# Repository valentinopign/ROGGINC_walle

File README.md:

# ROGGINC_walle
Proyecto final que encabezamos durante nuestra estadia en 7mo año para la materia de "Proyecto y diseño electronico"

Inspirados por la icónica película de Disney, tomamos la decisión
de modelar nuestro proyecto tomando la forma del entrañable
personaje principal, Wall-E. Este robot carismático se ha
convertido en un ícono, y decidimos emular su diseño distintivo
para crear un dispositivo interactivo y encantador.
Para lograr este objetivo, optamos por utilizar la tecnología de
impresión 3D para recrear no solo la forma general de Wall-E,
sino también sus característicos engranajes, añadiendo
autenticidad y detalle a nuestro proyecto. La impresión 3D nos
proporcionó la flexibilidad necesaria para capturar la esencia del
personaje de manera precisa y personalizada.
El enfoque principal de nuestro proyecto fue desarrollar un robot
capaz de moverse e interactuar de manera amigable con las
personas, y la elección de Wall-E como inspiración nos
proporcionó una base sólida para lograr este objetivo. Su diseño
único y su personalidad afectuosa sirvieron como punto de
partida para crear un dispositivo que no solo fuera funcional, sino
también emocionalmente atractivo.

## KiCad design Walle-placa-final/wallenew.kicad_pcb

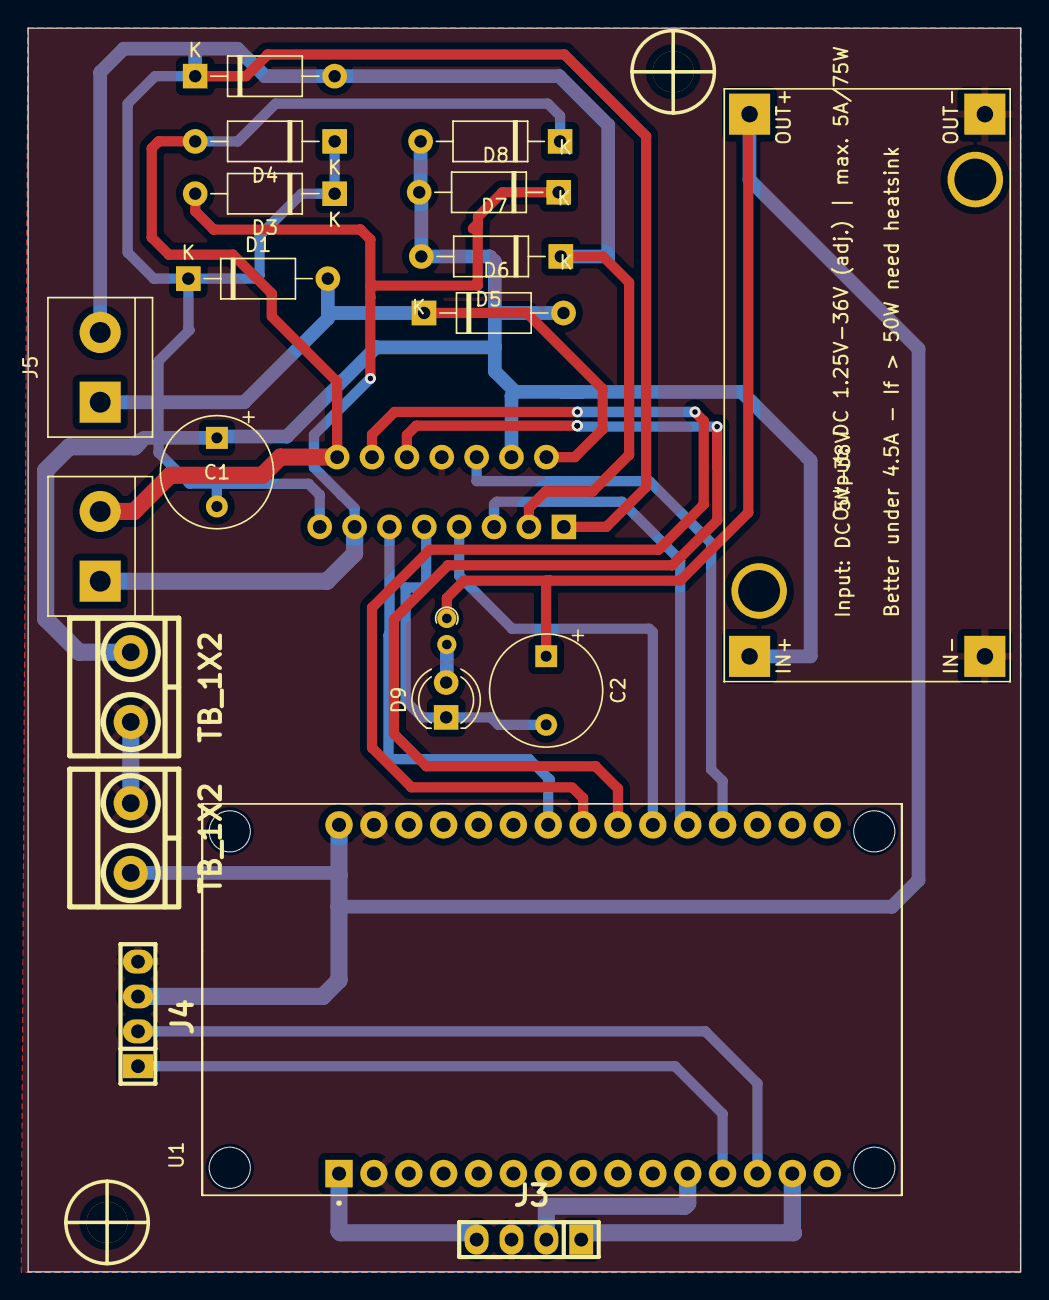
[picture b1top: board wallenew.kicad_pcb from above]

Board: 2 copper layers, 72.3 x 90.6 mm, 23 parts (1 on the bottom side), 17 nets.

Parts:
C1, C2: 220uF; CP_Radial_Tantal_D8.0mm_P5.00mm
D1, D2, D3, D4, D5, D6, D7, D8: DIODE; D_A-405_P10.16mm_Horizontal
D9: LED; LED_D4.0mm
H1, H2: Mounting_Hole; hole_3mm
J1, J2: TB_1X2; BORNERA2_AZUL
J3, J4: Conn_01x04; pin_strip_4
J5, J6: TB_1X2; TerminalBlock_bornier-2_P5.08mm
PS1: XL4005_DC-DC
R1: R; R_Axial_DIN0204_L3.6mm_D1.6mm_P1.90mm_Vertical
U1: ESP32-DEVKIT-V1; MODULE_ESP32_DEVKIT_V1
U2: L298N; TO-220-15_P2.54x2.54mm_StaggerOdd_Lead4.58mm_Vertical

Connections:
5V: C2.1, J1.1, J4.3, PS1.3 (OUT+), R1.1, U1.30 (VIN)
/3.3V: J3.4, U1.1 (3V3)
/PWM1: U1.19 (D34), U2.6 (EnA)
/PWM2: U1.24 (D26), U2.11 (EnB)
/RX: J4.2, U1.13 (TX0)
/SCL: J3.1, U1.14 (D22)
/SDA: J3.2, U1.11 (D21)
/TX: J4.1, U1.12 (RX0)
/in1: U1.20 (D35), U2.5 (IN1)
/in2: U1.21 (D32), U2.7 (IN2)
/in3: U1.22 (D33), U2.10 (IN3)
/in4: U1.23 (D25), U2.12 (IN4)
GND: J1.2, J2.1, J3.3, J4.4, PS1.2 (IN-), PS1.4 (OUT-), U1.2 (GND), U1.29 (GND), U2.8 (GND)
unnamed: C1.1, C1.2, D1.1 (A), D1.2 (K), D2.1 (A), D2.2 (K), D3.1 (A), D4.1 (A), D4.2 (K), D5.1 (A), D5.2 (K), D6.1 (A), D6.2 (K), D7.2 (K), D8.1 (A), D8.2 (K), J2.2, J5.1, J5.2, J6.2, PS1.1 (IN+), U2.1 (SENSE_A), U2.2 (OUT1), U2.3 (OUT2), U2.4 (Vs), U2.14 (OUT4), U2.15 (SENSE_B)
unnamed: D3.2 (K), D7.1 (A), J6.1, U2.13 (OUT3)
unnamed: D9.2 (A), R1.2
unnamed: C2.2, D9.1 (K), U2.9 (Vss)

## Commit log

2023-11-24 Piezas 3D
    Aqui se encuentra todas las piezas 3D del walle.
2023-11-24 PCB & SCH
    Aqui se encuentra el PCB y el SHC del walle
2023-11-24 Codigo
    Codigo del control bluetooth del Wall-e
2023-11-24 Create Piezas-3D-walle
2023-11-24 Piezas 3D
    Contiene todas las piezas 3D
2023-11-24 Piezas 3D
    Contiene todas las piezas 3D del walle utilizadas en este proyecto
